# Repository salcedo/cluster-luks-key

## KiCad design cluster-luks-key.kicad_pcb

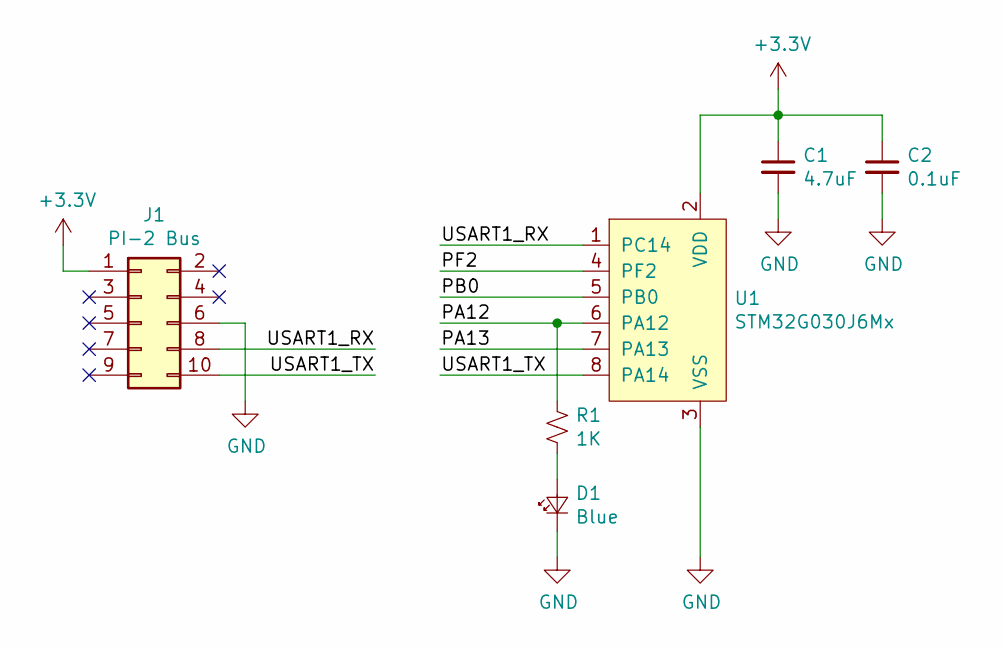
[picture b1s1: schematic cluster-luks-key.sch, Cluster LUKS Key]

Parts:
C1: 4.7uF; C_0603_1608Metric
C2: 0.1uF; C_0603_1608Metric
D1: Blue; LED_0603_1608Metric
J1: PI-2 Bus; PinSocket_2x05_P2.54mm_Horizontal
R1: 1K; R_0603_1608Metric
U1: STM32G030J6Mx; SO-8_3.9x4.9mm_P1.27mm

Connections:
+3V3: C1.1, C2.1, J1.1, U1.2 (VDD)
/PA12: R1.2, U1.6 (PA12)
/PA13: U1.7 (PA13)
/PB0: U1.5 (PB0)
/PF2: U1.4 (PF2)
/USART1_RX: J1.8, U1.1 (PC14)
/USART1_TX: J1.10, U1.8 (PA14)
GND: C1.2, C2.2, D1.1 (K), J1.6, U1.3 (VSS)
unnamed: D1.2 (A), R1.1

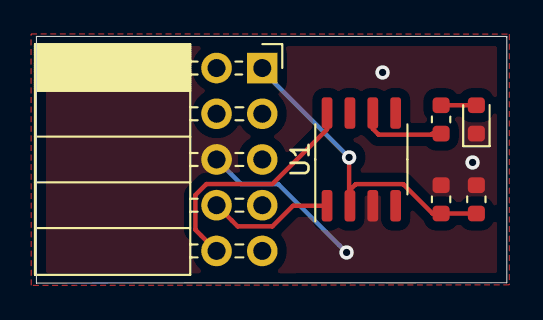
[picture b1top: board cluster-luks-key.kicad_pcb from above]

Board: 2 copper layers, 26.1 x 13.7 mm, 6 parts (0 on the bottom side), 6 nets.

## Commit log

2024-10-27 for archive
